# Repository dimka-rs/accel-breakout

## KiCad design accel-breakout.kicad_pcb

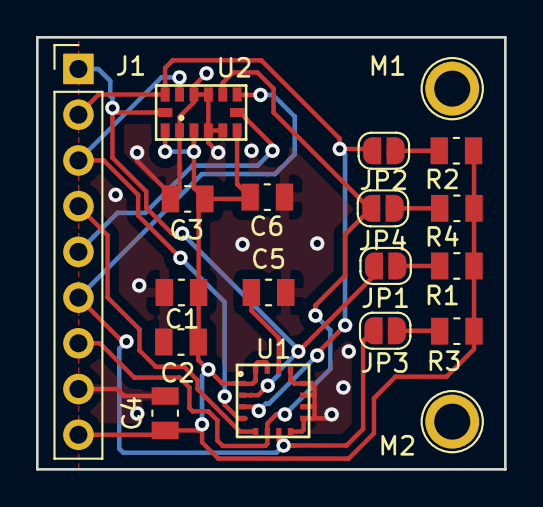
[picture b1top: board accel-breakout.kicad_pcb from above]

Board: 2 copper layers, 26.0 x 24.0 mm, 19 parts (0 on the bottom side), 14 nets.

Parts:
C1, C3: 10u; C_0805_2012Metric
C2, C4: 0.1u; C_0805_2012Metric
C5: 1n; C_0805_2012Metric
C6: 100n; C_0805_2012Metric
J1: Conn_01x09; PinHeader_1x09_P2.54mm_Vertical
JP1, JP2, JP3, JP4: SolderJumper_2_Open; SolderJumper-2_P1.3mm_Open_RoundedPad1.0x1.5mm
M1, M2: TestPoint_Plated_Hole_D2.0mm
R1, R2, R3, R4: 10k; R_0805_2012Metric
U1: L3GD20; LGA-16
U2: LIS302DL

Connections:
+3V3: C1.1, C2.1, C3.1, C4.1, C6.1, J1.9, R1.1, R2.1, R3.1, R4.1, U1.1, U1.15, U1.16, U2.1, U2.3, U2.6
GND: C1.2, C2.2, C3.2, C4.2, C5.2, C6.2, J1.8, U1.8, U1.9, U1.10, U1.11, U1.12, U1.13, U2.2, U2.4, U2.5, U2.10, U2.11
unnamed: C5.1, U1.14
unnamed: J1.1, JP1.2, U1.2, U2.14
unnamed: J1.2, JP2.2, U1.3, U2.13
unnamed: J1.3, U1.4, U2.12
unnamed: J1.4, U1.5
unnamed: J1.5, U2.7
unnamed: J1.6, JP3.2, U1.7, U2.8
unnamed: J1.7, JP4.2, U1.6, U2.9
unnamed: JP1.1, R1.2
unnamed: JP2.1, R2.2
unnamed: JP3.1, R3.2
unnamed: JP4.1, R4.2

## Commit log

2018-04-03 added L3GD20
2018-04-04 sch done
2018-04-05 pcb done
2018-04-05 pcb: added b.silk
2018-04-05 added gerbers
